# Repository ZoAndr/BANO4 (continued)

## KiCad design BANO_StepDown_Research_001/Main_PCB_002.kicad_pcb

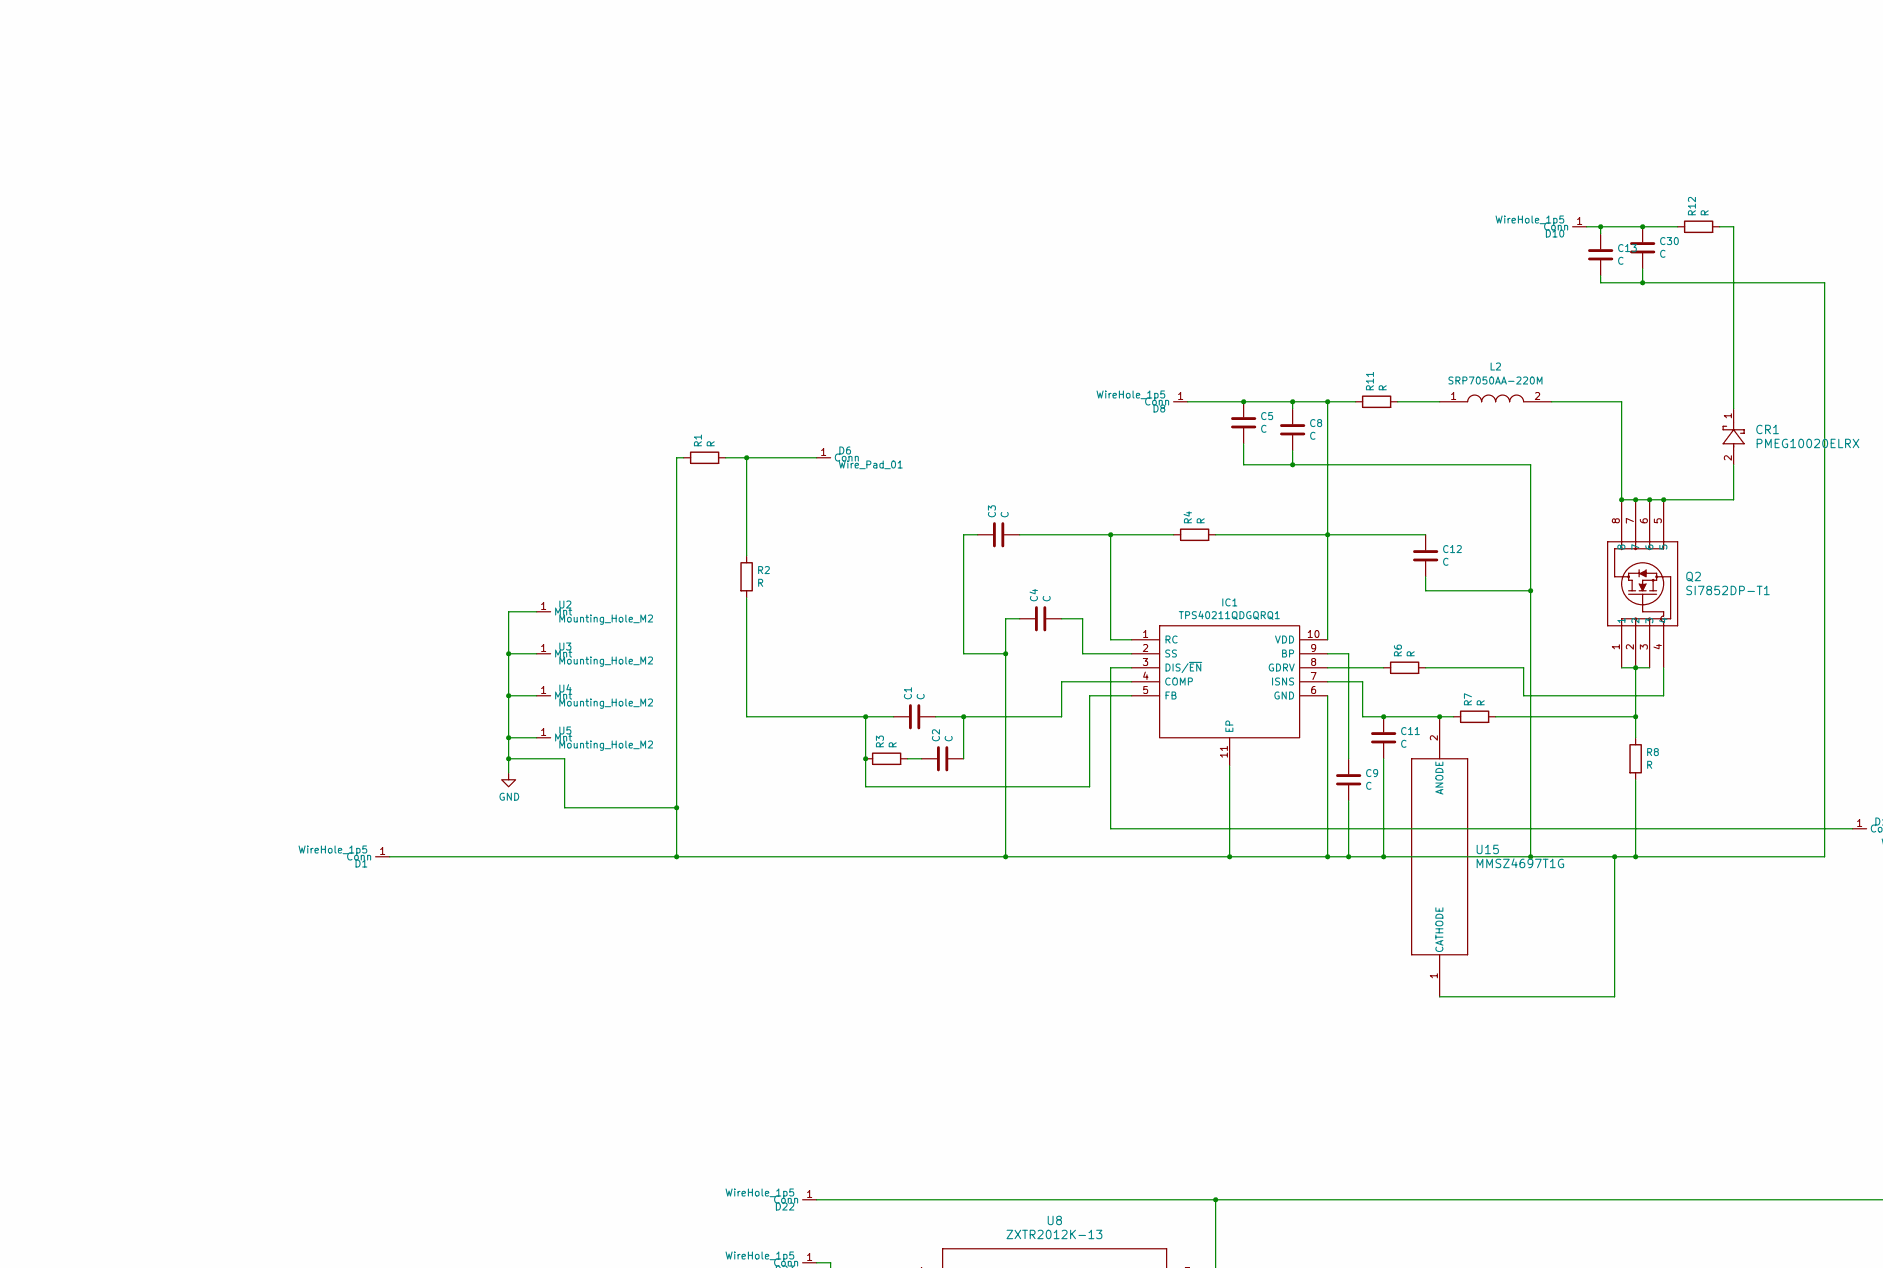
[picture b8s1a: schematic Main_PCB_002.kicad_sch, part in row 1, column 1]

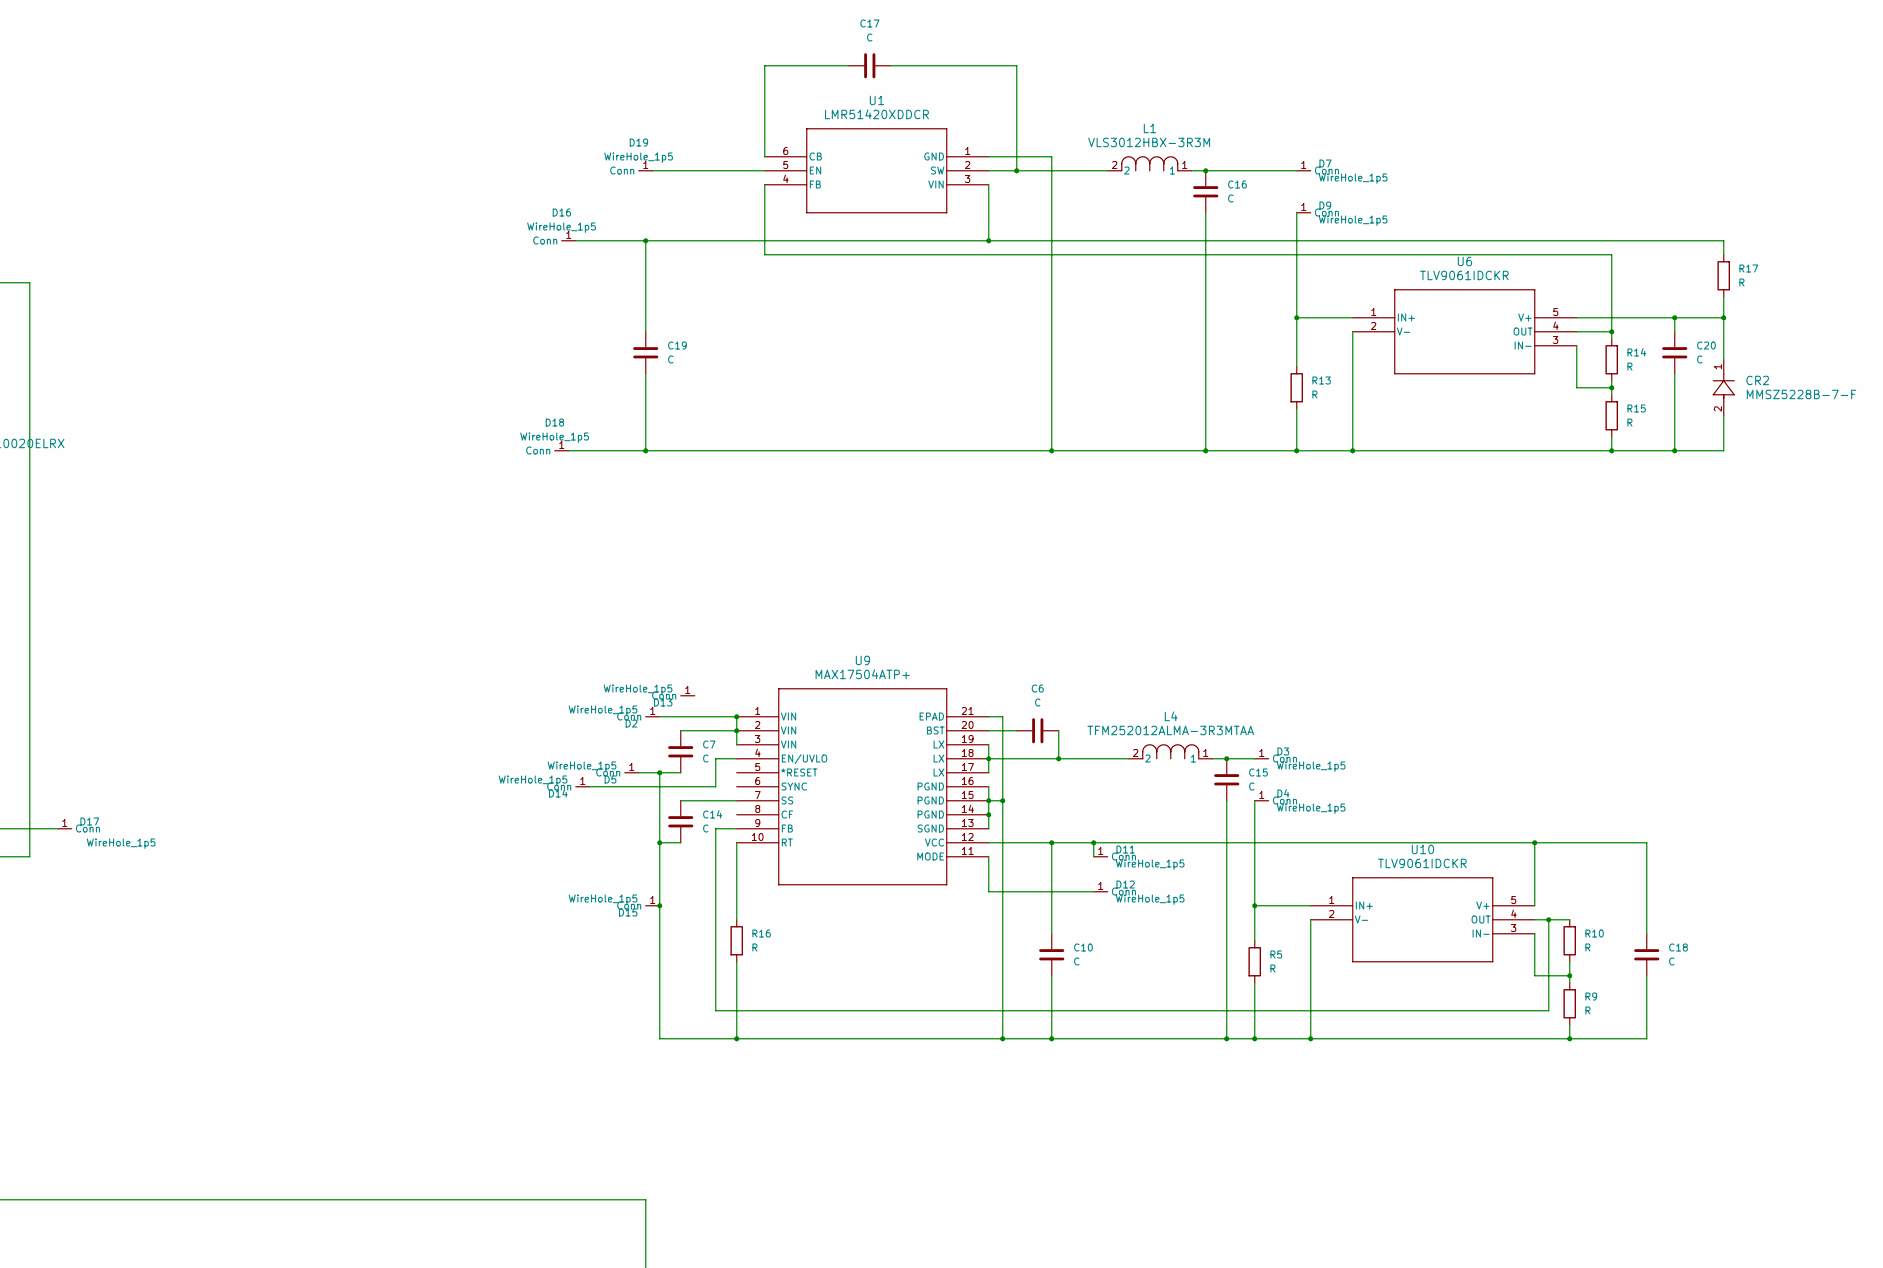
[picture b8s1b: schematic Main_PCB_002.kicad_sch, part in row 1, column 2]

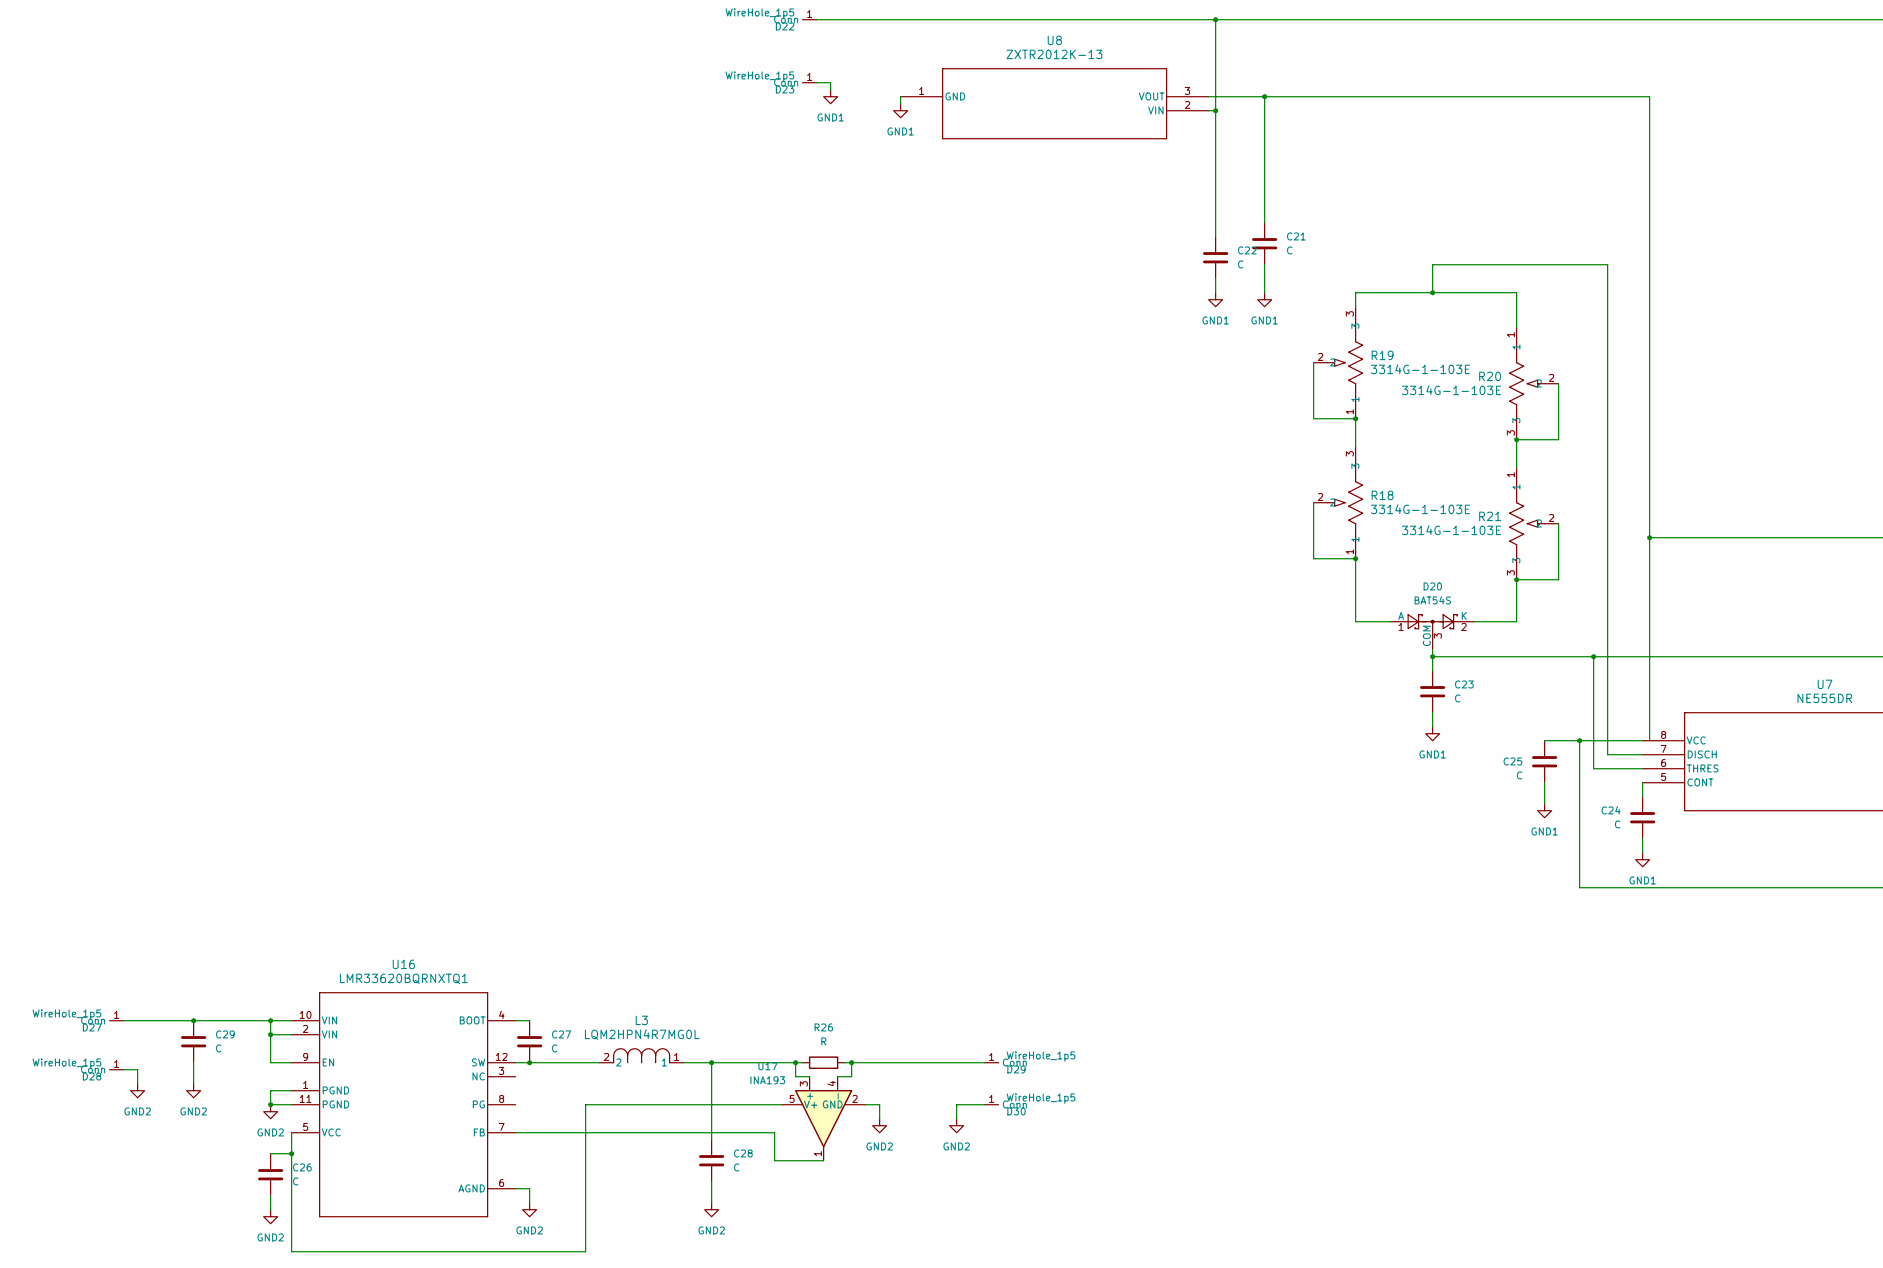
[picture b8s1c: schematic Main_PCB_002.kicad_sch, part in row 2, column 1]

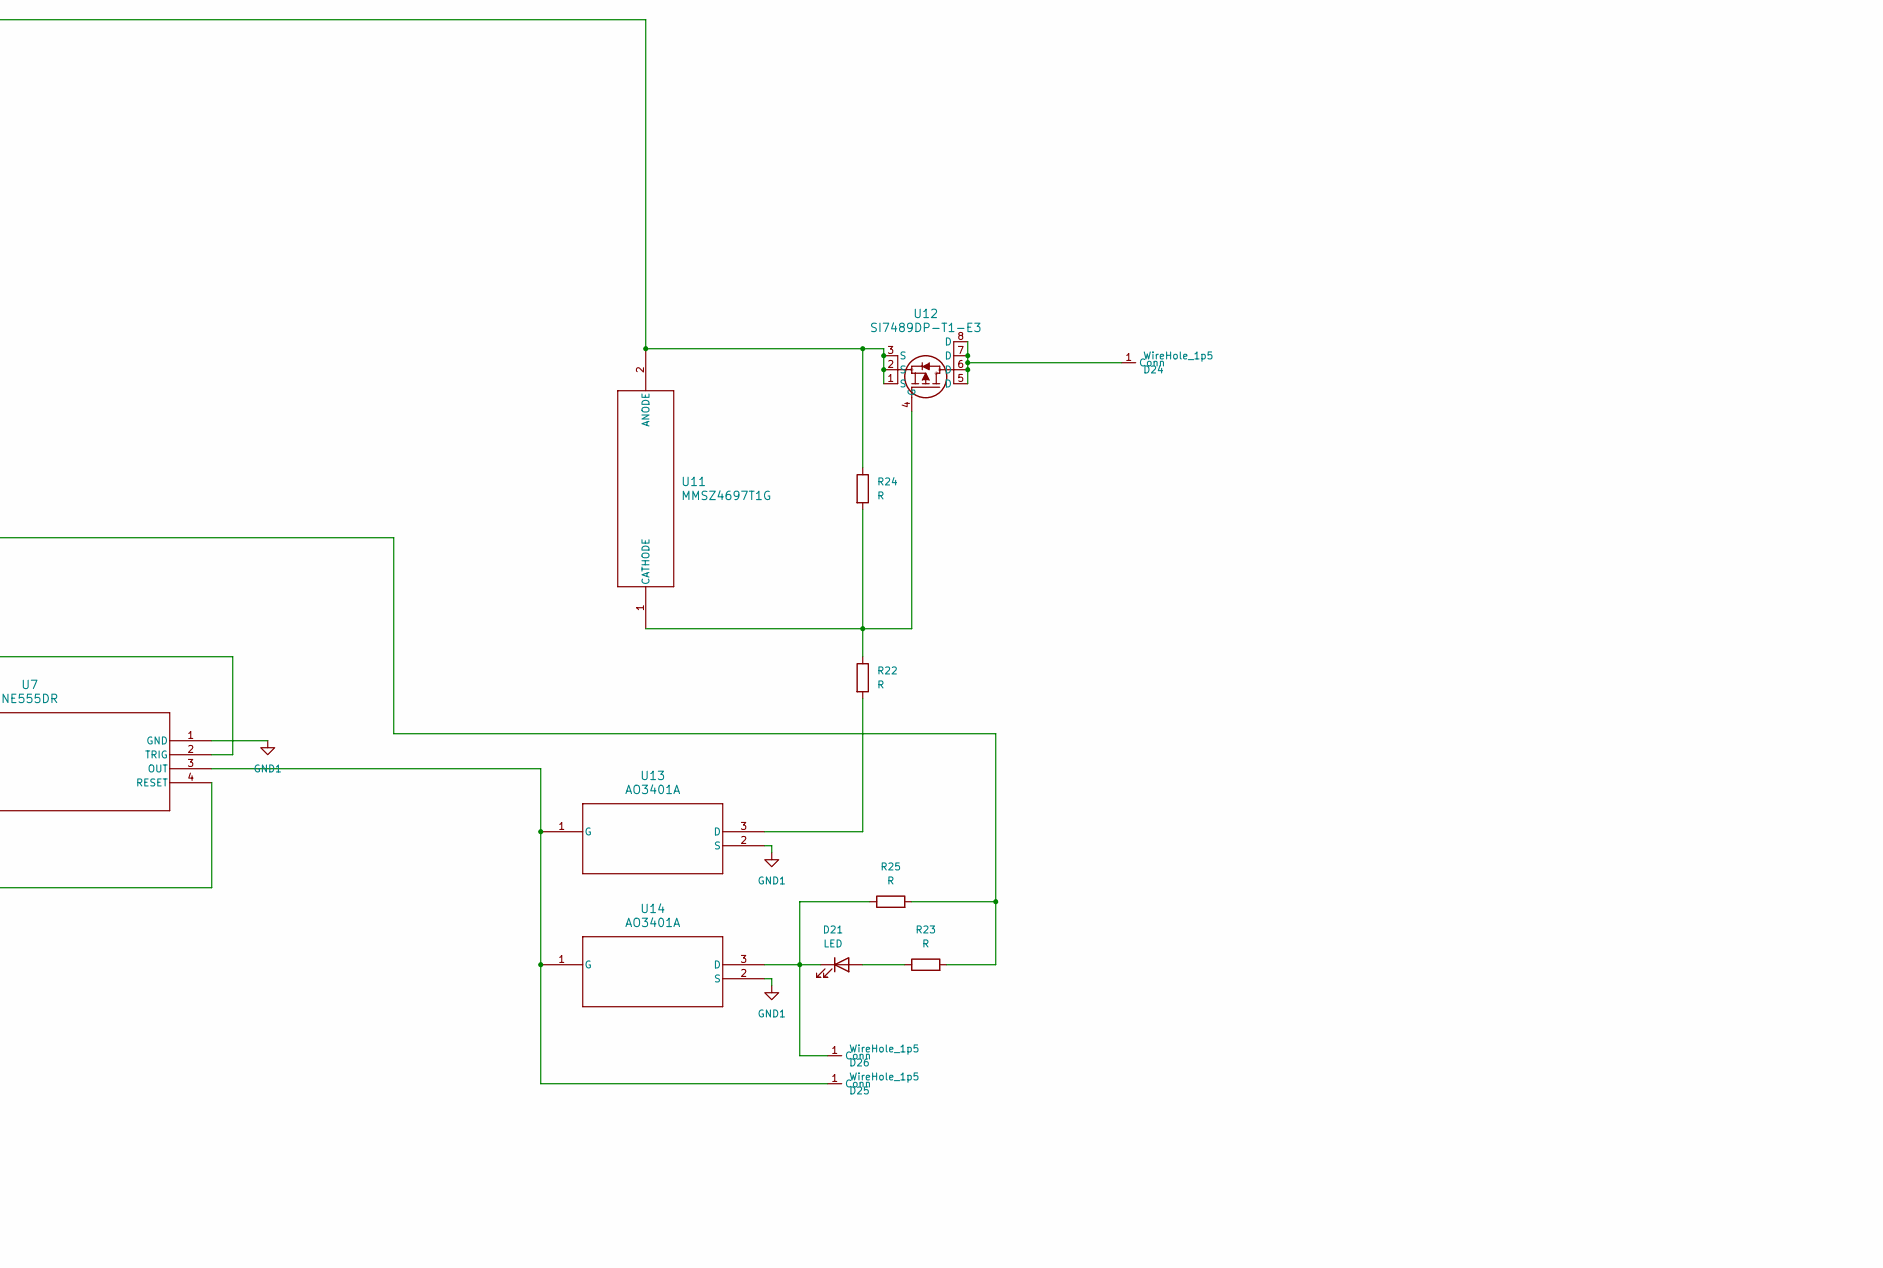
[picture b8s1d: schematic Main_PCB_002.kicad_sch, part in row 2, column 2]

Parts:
C1, C2, C3, C4, C5, C7, C8, C9, C10, C11, C15, C16, C18, C19, C23, C25, C28, C29, C30: C; C_0805_2012Metric_Pad1.18x1.45mm_HandSolder
C6, C12, C14, C17, C20, C21, C22, C24, C26, C27: C; C_0603_1608Metric_Pad1.08x0.95mm_HandSolder
C13: C; C_1206_3216Metric_Pad1.33x1.80mm_HandSolder
CR1: PMEG10020ELRX; CFP3_SOD123W_NEX
CR2: MMSZ5228B-7-F; SOD123_DIO
D1, D2, D3, D4, D5, D7, D8, D9, D10, D11, D12, D13, D14, D15, D16, D17, D18, D19, D22, D23, D24, D25, D26, D27, D28, D29, D30: WireHole_1p5; WireHole_1p2
D6: Wire_Pad_01; WireHole_1p5
D20: BAT54S; SOT-23
D21: LED; LED_0603_1608Metric_Pad1.05x0.95mm_HandSolder
IC1: TPS40211QDGQRQ1; DRC0010J; Manufacturer_Part_Number TPS40211QDGQRQ1; Mouser Part Number 595-TPS40211QDGQRQ1
L1: VLS3012HBX-3R3M; IND_VLS3012HBX-3R3M_TDK
L2: SRP7050AA-220M; IND_SRP7050AA_BRN; Manufacturer_Part_Number SRP7050AA-220M; Mouser Part Number 652-SRP7050AA-220M
L3: LQM2HPN4R7MG0L; IND_LQM2HPN4R7MG0L_MUR
L4: TFM252012ALMA-3R3MTAA; IND_TFM252012_TDK
Q2: SI7852DP-T1; POWERPAK_SO-8_SINGLE_VIS
R1, R2, R3, R4, R5, R6, R7, R9, R10, R11, R12, R13, R14, R15, R16, R17, R22, R23, R24, R25, R26: R; R_0603_1608Metric_Pad0.98x0.95mm_HandSolder
R8: R; R_0805_2012Metric_Pad1.20x1.40mm_HandSolder
R18, R19, R20, R21: 3314G-1-103E; POT_3314G
U1: LMR51420XDDCR; SOT23_DDC_TEX
U2, U3, U4, U5: Mounting_Hole_M2; WireHole_1p5
U6, U10: TLV9061IDCKR; DCK5_TEX
U7: NE555DR; D8
U8: ZXTR2012K-13; TO252-3L_DIO
U9: MAX17504ATP+; 21-0140_T2055&plus_4C_MXM
U11, U15: MMSZ4697T1G; SOD-123_ONS
U12: SI7489DP-T1-E3; MOSFET_65DP-T1-E3_VIS
U13, U14: AO3401A; SOT-23-3L_AOS
U16: LMR33620BQRNXTQ1; RNX0012B
U17: INA193; SOT-23-5

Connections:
GND: C3.1, C4.1, C5.2, C8.2, C9.2, C11.2, C12.2, C13.2, C30.2, D1.1 (Conn), IC1.6 (GND), IC1.11 (EP), R1.1, R8.2, U2.1 (Mnt), U3.1 (Mnt), U4.1 (Mnt), U5.1 (Mnt), U15.1 (CATHODE)
GND1: C21.2, C22.2, C23.2, C24.2, C25.2, D23.1 (Conn), U7.1 (GND), U8.1 (GND), U13.2 (S), U14.2 (S)
GND2: C26.2, C28.2, C29.2, D28.1 (Conn), D30.1 (Conn), U16.1 (PGND), U16.6 (AGND), U16.11 (PGND), U17.2 (GND)
unnamed: C2.1, R3.2
unnamed: C6.2, L4.2, U9.17 (LX), U9.18 (LX), U9.19 (LX)
unnamed: CR1.1, R12.2
unnamed: CR1.2, L2.2, Q2.5, Q2.6, Q2.7, Q2.8
unnamed: C7.1, D2.1 (Conn), U9.1 (VIN), U9.2 (VIN), U9.3 (VIN)
unnamed: C15.1, D3.1 (Conn), L4.1
unnamed: D4.1 (Conn), R5.1, U10.1 (IN+)
unnamed: D6.1 (Conn), R1.2, R2.1
unnamed: C16.1, D7.1 (Conn), L1.1
unnamed: C5.1, C8.1, C12.1, D8.1 (Conn), IC1.10 (VDD), R4.2, R11.1
unnamed: D9.1 (Conn), R13.1, U6.1 (IN+)
unnamed: C13.1, C30.1, D10.1 (Conn), R12.1
unnamed: C10.1, C18.1, D11.1 (Conn), U9.12 (VCC), U10.5 (V+)
unnamed: D12.1 (Conn), U9.11 (MODE)
unnamed: D14.1 (Conn), U9.4 (EN/UVLO)
unnamed: C7.2, C10.2, C14.2, C15.2, C18.2, D5.1 (Conn), D15.1 (Conn), R5.2, R9.1, R16.2, U9.13 (SGND), U9.14 (PGND), U9.15 (PGND), U9.16 (PGND), U9.21 (EPAD), U10.2 (V-)
unnamed: C19.1, D16.1 (Conn), R17.2, U1.3 (VIN)
unnamed: D17.1 (Conn), IC1.3 (DIS/~EN)
unnamed: C16.2, C19.2, C20.2, CR2.2, D18.1 (Conn), R13.2, R15.1, U1.1 (GND), U6.2 (V-)
unnamed: D19.1 (Conn), U1.5 (EN)
unnamed: D20.1 (A), R18.1, R18.2
unnamed: C23.1, D20.3 (COM), U7.2 (TRIG), U7.6 (THRES)
unnamed: D20.2 (K), R21.2, R21.3
unnamed: D21.2 (A), R23.1
unnamed: D21.1 (K), D26.1 (Conn), R25.1, U14.3 (D)
unnamed: C22.1, D22.1 (Conn), R24.1, U8.2 (VIN), U11.2 (ANODE), U12.1 (S), U12.2 (S), U12.3 (S)
unnamed: D24.1 (Conn), U12.5 (D), U12.6 (D), U12.7 (D), U12.8 (D)
unnamed: D25.1 (Conn), U7.3 (OUT), U13.1 (G), U14.1 (G)
unnamed: C29.1, D27.1 (Conn), U16.2 (VIN), U16.9 (EN), U16.10 (VIN)
unnamed: D29.1 (Conn), R26.2, U17.4 (-)
unnamed: C9.1, IC1.9 (BP)
unnamed: C1.2, C2.2, IC1.4 (COMP)
unnamed: C1.1, IC1.5 (FB), R2.2, R3.1
unnamed: IC1.8 (GDRV), R6.1
unnamed: C11.1, IC1.7 (ISNS), R7.1, U15.2 (ANODE)
unnamed: C3.2, IC1.1 (RC), R4.1
unnamed: C4.2, IC1.2 (SS)
unnamed: L2.1, R11.2
unnamed: Q2.1, Q2.2, Q2.3, R7.2, R8.1
unnamed: Q2.4, R6.2
unnamed: R18.3, R19.1, R19.2
unnamed: R20.2, R20.3, R21.1
unnamed: C17.1, U1.6 (CB)
unnamed: R14.2, U1.4 (FB), U6.4 (OUT)
unnamed: C17.2, L1.2, U1.2 (SW)
unnamed: R14.1, R15.2, U6.3 (IN-)
unnamed: C20.1, CR2.1, R17.1, U6.5 (V+)
unnamed: C24.1, U7.5 (CONT)
unnamed: R19.3, R20.1, U7.7 (DISCH)
unnamed: C25.1, U7.4 (RESET), U7.8 (VCC)
unnamed: C21.1, R23.2, R25.2, U8.3 (VOUT)
unnamed: C6.1, U9.20 (BST)
unnamed: R16.1, U9.10 (RT)
unnamed: C14.1, U9.7 (SS)
unnamed: R9.2, R10.1, U10.3 (IN-)
unnamed: R10.2, U9.9 (FB), U10.4 (OUT)
unnamed: R22.1, R24.2, U11.1 (CATHODE), U12.4 (G)
unnamed: R22.2, U13.3 (D)
unnamed: C27.1, U16.4 (BOOT)
unnamed: U16.7 (FB), U17.1
unnamed: C27.2, L3.2, U16.12 (SW)
unnamed: C26.1, U16.5 (VCC), U17.5 (V+)
unnamed: C28.1, L3.1, R26.1, U17.3 (+)

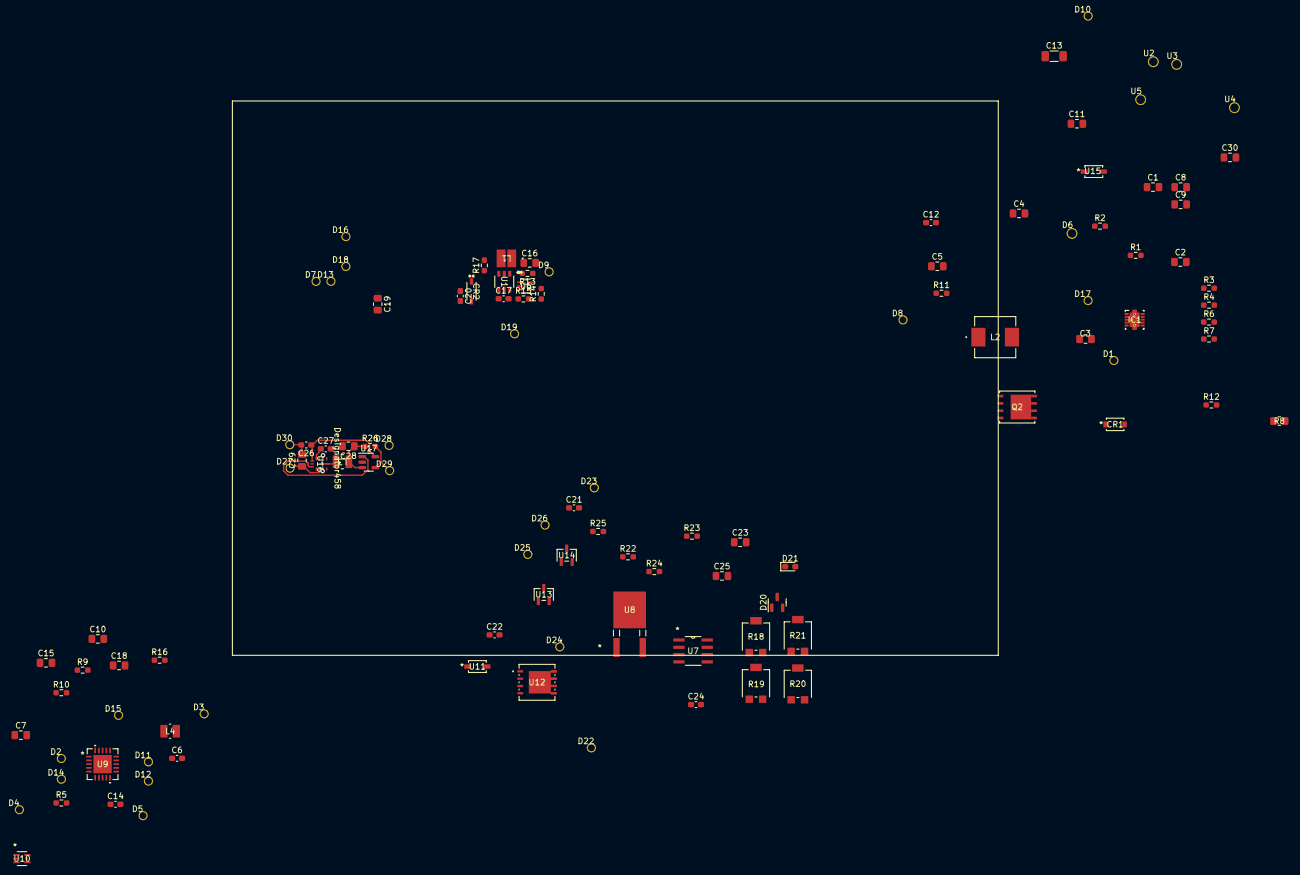
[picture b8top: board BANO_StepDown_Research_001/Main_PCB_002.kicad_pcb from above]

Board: 2 copper layers, 111 parts (0 on the bottom side), 66 nets.

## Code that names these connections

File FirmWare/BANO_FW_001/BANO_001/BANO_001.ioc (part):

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Mcu.Name=STM32G031G(4-6-8)Ux
Mcu.Package=UFQFPN28
Mcu.UserName=STM32G031G8Ux
PA0.Mode=IN0
PA0.Signal=ADC1_IN0
PA1.Mode=IN1
PA1.Signal=ADC1_IN1
PA15.Signal=GPIO_Output
PA2.Mode=Asynchronous
PA2.Signal=USART2_TX
PA3.Mode=Asynchronous
PA3.Signal=USART2_RX
PA4.Signal=GPXTI4
PB0.GPIOParameters=PinState
PB0.PinState=GPIO_PIN_SET
PB0.Signal=GPIO_Output
PB1.Signal=GPIO_Output
PB4.Signal=GPIO_Input
PB5.Signal=GPIO_Input
PB6.Mode=Asynchronous
PB6.Signal=USART1_TX
PB7.Mode=Asynchronous
PB7.Signal=USART1_RX
PC6.Signal=GPIO_Output
RCC.HSE_VALUE=8000000
RCC.SYSCLKFreq_VALUE=16000000
board=custom

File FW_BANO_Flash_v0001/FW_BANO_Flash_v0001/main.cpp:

/*
 * FW_BANO_Flash_v0001.cpp
 *
 * Created: 18.05.2019 23:15:44
 * Author : С_Белл
 */ 

/*
 * FW_BANO_Flash_v001.c
 *
 * Created: 18.05.2019 23:00:03
 * Author : С_Белл
 */ 

//
//
//               Reset/ADC0 PB5        VCC
//
//     XTAL1/CLK1/OC1B/ADC3 PB3        PB2(SCK/SCL/ADC1/T0/INT0
//
//     XTAL2/CLKO/OC1B/ADC2 PB4        PB1 MISO/D0/AIN1/OC0B/OC1A
//
//                          GND        PB0 MOSI/DI/SDA/AIN0/OC0A/OC1A/AREF
//
//


/*
 * BANO_Flash_001.c
 *
 * Created: 18.05.2019 16:46:59
 * Author : Zobenko
 */

#include <avr/io.h>
#include <avr/interrupt.h>

#define DDR_SYNC  0x04  // PortB2, pin 7
#define DDR_FLASH 0x02  // PortB1, pin 6

int main() {
TCCR1 = (1<<CS02)|(1<<CS00);
TIFR = (1<<TOV1);
TIMSK = (1<<TOIE1);
// DDRB = 1;
// PORTB = 1;
DDRB = (DDR_SYNC | DDR_FLASH);
PORTB = DDR_SYNC;


sei();
while (1) {
//PORTB=0; // Don't optimize out
}
}

#define FLS_INTVL 60
#define FLS_DLY 15
#define FLS_PAUSE 500
#define SYNC_PERIOD 100

//PINB2/PORTB2 - Sync
//PORTB4 - Flash Out

ISR(TIMER1_OVF_vect) 
{
    static int cntr = 0;

    if( (cntr == FLS_INTVL * 0) || (cntr == (FLS_INTVL * 1)) || (cntr == (FLS_INTVL * 2)) )
    {
//        DDRB  |= DDR_FLASH;
        PORTB |= DDR_FLASH;

        if(cntr == FLS_INTVL * 0){PORTB |= DDR_SYNC; DDRB |= DDR_SYNC;}

        cntr ++;
    }
    else if( (cntr == FLS_INTVL * 0 + FLS_DLY) || (cntr == (FLS_INTVL * 1 + FLS_DLY)) || (cntr == (FLS_INTVL * 2 + FLS_DLY)) )
    {
        // DDRB &= ~DDR_SYNC;
        PORTB &= ~(DDR_FLASH | DDR_SYNC);
        cntr ++;
    }
    else if(  cntr == FLS_PAUSE  )
    {
		DDRB &= 0xFB; //~(DDR_SYNC);
        PORTB &= ~(DDR_SYNC);
        cntr ++;
    }
    else if(  (cntr > FLS_PAUSE)  &&  (cntr < (FLS_PAUSE + SYNC_PERIOD))  )
    {

        if((PINB & DDR_SYNC)== DDR_SYNC)
        {
            DDRB |= (DDR_SYNC);
            PORTB |= (DDR_FLASH | DDR_SYNC);
            cntr = 1;
    	}
        else
        {
            cntr ++;
        }
    }
    else if(cntr >= (FLS_PAUSE + SYNC_PERIOD))
    {
        // DDRB = 1;
        cntr = 0;
    }
    else
    {
        cntr ++;
    }

}










/*
#include <avr/io.h>
#include <avr/interrupt.h>

int cntr = 0;

ISR(TIMER1_OVF_vect) {
	
	cntr ++;
	
	if(cntr == 950
	{
		DDRB = 1;
		PORTB=1;
	}
	else if(cntr > 1000)
	{
		cntr = 0;
		DDRB = 0;
		PORTB=0;
	}

	
}

int main() {
	TCCR1 = (1<<CS02)|(1<<CS00);
	TIFR = (1<<TOV1);
	TIMSK = (1<<TOIE1);
	sei();
	while (1) {
	//	PORTB=0; // Don't optimize out
	}
}
*/

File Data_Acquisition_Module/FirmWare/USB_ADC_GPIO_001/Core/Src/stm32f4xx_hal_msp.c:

/* USER CODE BEGIN Header */
/**
  ******************************************************************************
  * @file         stm32f4xx_hal_msp.c
  * @brief        This file provides code for the MSP Initialization
  *               and de-Initialization codes.
  ******************************************************************************
  * @attention
  *
  * <h2><center>&copy; Copyright (c) 2022 STMicroelectronics.
  * All rights reserved.</center></h2>
  *
  * This software component is licensed by ST under BSD 3-Clause license,
  * the "License"; You may not use this file except in compliance with the
  * License. You may obtain a copy of the License at:
  *                        opensource.org/licenses/BSD-3-Clause
  *
  ******************************************************************************
  */
/* USER CODE END Header */

/* Includes ------------------------------------------------------------------*/
#include "main.h"
/* USER CODE BEGIN Includes */

/* USER CODE END Includes */

/* Private typedef -----------------------------------------------------------*/
/* USER CODE BEGIN TD */

/* USER CODE END TD */

/* Private define ------------------------------------------------------------*/
/* USER CODE BEGIN Define */

/* USER CODE END Define */

/* Private macro -------------------------------------------------------------*/
/* USER CODE BEGIN Macro */

/* USER CODE END Macro */

/* Private variables ---------------------------------------------------------*/
/* USER CODE BEGIN PV */

/* USER CODE END PV */

/* Private function prototypes -----------------------------------------------*/
/* USER CODE BEGIN PFP */

/* USER CODE END PFP */

/* External functions --------------------------------------------------------*/
/* USER CODE BEGIN ExternalFunctions */

/* USER CODE END ExternalFunctions */

/* USER CODE BEGIN 0 */

/* USER CODE END 0 */
/**
  * Initializes the Global MSP.
  */
void HAL_MspInit(void)
{
  /* USER CODE BEGIN MspInit 0 */

  /* USER CODE END MspInit 0 */

  __HAL_RCC_SYSCFG_CLK_ENABLE();
  __HAL_RCC_PWR_CLK_ENABLE();

  /* System interrupt init*/

  /* USER CODE BEGIN MspInit 1 */

  /* USER CODE END MspInit 1 */
}

/**
* @brief ADC MSP Initialization
* This function configures the hardware resources used in this example
* @param hadc: ADC handle pointer
* @retval None
*/
void HAL_ADC_MspInit(ADC_HandleTypeDef* hadc)
{
  GPIO_InitTypeDef GPIO_InitStruct = {0};
  if(hadc->Instance==ADC1)
  {
  /* USER CODE BEGIN ADC1_MspInit 0 */

  /* USER CODE END ADC1_MspInit 0 */
    /* Peripheral clock enable */
    __HAL_RCC_ADC1_CLK_ENABLE();

    __HAL_RCC_GPIOA_CLK_ENABLE();
    /**ADC1 GPIO Configuration
    PA0-WKUP     ------> ADC1_IN0
    PA1     ------> ADC1_IN1
    PA2     ------> ADC1_IN2
    */
    GPIO_InitStruct.Pin = GPIO_PIN_0|GPIO_PIN_1|GPIO_PIN_2;
    GPIO_InitStruct.Mode = GPIO_MODE_ANALOG;
    GPIO_InitStruct.Pull = GPIO_NOPULL;
    HAL_GPIO_Init(GPIOA, &GPIO_InitStruct);

  /* USER CODE BEGIN ADC1_MspInit 1 */

  /* USER CODE END ADC1_MspInit 1 */
  }
  else if(hadc->Instance==ADC2)
  {
  /* USER CODE BEGIN ADC2_MspInit 0 */

  /* USER CODE END ADC2_MspInit 0 */
    /* Peripheral clock enable */
    __HAL_RCC_ADC2_CLK_ENABLE();

    __HAL_RCC_GPIOA_CLK_ENABLE();
    __HAL_RCC_GPIOC_CLK_ENABLE();
    /**ADC2 GPIO Configuration
    PA6     ------> ADC2_IN6
    PA7     ------> ADC2_IN7
    PC4     ------> ADC2_IN14
    */
    GPIO_InitStruct.Pin = GPIO_PIN_6|GPIO_PIN_7;
    GPIO_InitStruct.Mode = GPIO_MODE_ANALOG;
    GPIO_InitStruct.Pull = GPIO_NOPULL;
    HAL_GPIO_Init(GPIOA, &GPIO_InitStruct);

    GPIO_InitStruct.Pin = GPIO_PIN_4;
    GPIO_InitStruct.Mode = GPIO_MODE_ANALOG;
    GPIO_InitStruct.Pull = GPIO_NOPULL;
    HAL_GPIO_Init(GPIOC, &GPIO_InitStruct);

  /* USER CODE BEGIN ADC2_MspInit 1 */

  /* USER CODE END ADC2_MspInit 1 */
  }
  else if(hadc->Instance==ADC3)
  {
  /* USER CODE BEGIN ADC3_MspInit 0 */

  /* USER CODE END ADC3_MspInit 0 */
    /* Peripheral clock enable */
    __HAL_RCC_ADC3_CLK_ENABLE();

    __HAL_RCC_GPIOC_CLK_ENABLE();
    /**ADC3 GPIO Configuration
    PC1     ------> ADC3_IN11
    */
    GPIO_InitStruct.Pin = GPIO_PIN_1;
    GPIO_InitStruct.Mode = GPIO_MODE_ANALOG;
    GPIO_InitStruct.Pull = GPIO_NOPULL;
    HAL_GPIO_Init(GPIOC, &GPIO_InitStruct);

  /* USER CODE BEGIN ADC3_MspInit 1 */

  /* USER CODE END ADC3_MspInit 1 */
  }

}

/**
* @brief ADC MSP De-Initialization
* This function freeze the hardware resources used in this example
* @param hadc: ADC handle pointer
* @retval None
*/
void HAL_ADC_MspDeInit(ADC_HandleTypeDef* hadc)
{
  if(hadc->Instance==ADC1)
  {
  /* USER CODE BEGIN ADC1_MspDeInit 0 */

  /* USER CODE END ADC1_MspDeInit 0 */
    /* Peripheral clock disable */
    __HAL_RCC_ADC1_CLK_DISABLE();

    /**ADC1 GPIO Configuration
    PA0-WKUP     ------> ADC1_IN0
    PA1     ------> ADC1_IN1
    PA2     ------> ADC1_IN2
    */
    HAL_GPIO_DeInit(GPIOA, GPIO_PIN_0|GPIO_PIN_1|GPIO_PIN_2);

  /* USER CODE BEGIN ADC1_MspDeInit 1 */

  /* USER CODE END ADC1_MspDeInit 1 */
  }
  else if(hadc->Instance==ADC2)
  {
  /* USER CODE BEGIN ADC2_MspDeInit 0 */

  /* USER CODE END ADC2_MspDeInit 0 */
    /* Peripheral clock disable */
    __HAL_RCC_ADC2_CLK_DISABLE();

    /**ADC2 GPIO Configuration
    PA6     ------> ADC2_IN6
    PA7     ------> ADC2_IN7
    PC4     ------> ADC2_IN14
    */
    HAL_GPIO_DeInit(GPIOA, GPIO_PIN_6|GPIO_PIN_7);

    HAL_GPIO_DeInit(GPIOC, GPIO_PIN_4);

  /* USER CODE BEGIN ADC2_MspDeInit 1 */

  /* USER CODE END ADC2_MspDeInit 1 */
  }
  else if(hadc->Instance==ADC3)
  {
  /* USER CODE BEGIN ADC3_MspDeInit 0 */

  /* USER CODE END ADC3_MspDeInit 0 */
    /* Peripheral clock disable */
    __HAL_RCC_ADC3_CLK_DISABLE();

    /**ADC3 GPIO Configuration
    PC1     ------> ADC3_IN11
    */
    HAL_GPIO_DeInit(GPIOC, GPIO_PIN_1);

  /* USER CODE BEGIN ADC3_MspDeInit 1 */

  /* USER CODE END ADC3_MspDeInit 1 */
  }

}

/**
* @brief TIM_Base MSP Initialization
* This function configures the hardware resources used in this example
* @param htim_base: TIM_Base handle pointer
* @retval None
*/
void HAL_TIM_Base_MspInit(TIM_HandleTypeDef* htim_base)
{
  if(htim_base->Instance==TIM2)
  {
  /* USER CODE BEGIN TIM2_MspInit 0 */

  /* USER CODE END TIM2_MspInit 0 */
    /* Peripheral clock enable */
    __HAL_RCC_TIM2_CLK_ENABLE();
    /* TIM2 interrupt Init */
    HAL_NVIC_SetPriority(TIM2_IRQn, 0, 0);
    HAL_NVIC_EnableIRQ(TIM2_IRQn);
  /* USER CODE BEGIN TIM2_MspInit 1 */

  /* USER CODE END TIM2_MspInit 1 */
  }

}

/**
* @brief TIM_Base MSP De-Initialization
* This function freeze the hardware resources used in this example
* @param htim_base: TIM_Base handle pointer
* @retval None
*/
void HAL_TIM_Base_MspDeInit(TIM_HandleTypeDef* htim_base)
{
  if(htim_base->Instance==TIM2)
  {
  /* USER CODE BEGIN TIM2_MspDeInit 0 */

  /* USER CODE END TIM2_MspDeInit 0 */
    /* Peripheral clock disable */
    __HAL_RCC_TIM2_CLK_DISABLE();

    /* TIM2 interrupt DeInit */
    HAL_NVIC_DisableIRQ(TIM2_IRQn);
  /* USER CODE BEGIN TIM2_MspDeInit 1 */

  /* USER CODE END TIM2_MspDeInit 1 */
  }

}

/* USER CODE BEGIN 1 */

/* USER CODE END 1 */

/************************ (C) COPYRIGHT STMicroelectronics *****END OF FILE****/

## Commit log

2022-04-10 First schematic of Main Module
2022-04-16 PCB. Working 001
2022-04-17 PCB working 003
2022-04-23 Pcb working 004
2022-04-24 PCB working
2022-04-24 PCB on work
2022-04-27 PCB underwork
2022-04-29 PCB working on
2022-04-29 Firmware added
2022-05-29 Working with constructive
2022-06-05 Constructive
2022-06-08 Constructuve
2022-06-17 PCB+Solidworks
2022-06-19 Gerbers
2022-06-25 PCB for JLCPCB
2022-07-09 First PCB
2022-08-08 Corrections 001
2022-08-13 Lighting PCBs
2022-08-13 Lighting PCBs 02
2022-10-28 Start 2nd version
2022-10-30 Underwork 001
2022-11-01 Calculations in uCap
2022-11-01 Modeling in MicroCap
2022-11-03 Modeling of ... . Modeling.
2022-11-04 Control & Protections board
2022-11-05 Module of protections and control
2022-11-10 Layering 002
2022-11-26 Prototyping
2022-12-02 Prototyping 6 001
2022-12-11 Prototyping 06
2022-12-17 JLCPCB ordering 6X prototype
2022-12-23 Data_Acquisition_Module_001
2022-12-24 Protocol
2022-12-25 Protocol 002
2022-12-25 Firmware emulation
2023-01-03 Firmware 001
2023-08-25 PCB for radiated noise research
2023-08-27 PCB for radiated noise research 002
2023-08-27 Noise research for TSP40211 003
2023-09-03 Noise research for TSP40211 004
2023-09-07 Noise research for TSP40211 005
2023-11-01 BANO Step-Dn 001
2023-11-19 BANO Step-Dn 002
2024-02-07 BANO Step-Dn 003
2024-04-13 BANO Step-Dn 004
2024-04-27 BANO Step-Dn 004 Double DC 001
2024-05-05 BANO Step-Dn 004 Double DC 002
2024-05-06 PCB work
2024-05-15 PCB work 2
2024-06-06 BANO MainModule Double Strob
2024-07-07 PCB work 3
2024-07-21 PCB work 4
2024-07-25 PCB work 5
2024-07-26 PCB work 6
2024-08-03 MUZ2
2024-08-30 PCB work 7
2024-09-05 new machine
2024-09-05 Diagrams added
2024-10-06 Temperature prints
2024-10-21 MUZ 001
2024-11-20 MUZ 001 PCB 001
